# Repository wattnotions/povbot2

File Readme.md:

# POVbot - A Small Pi Zero FPV Robot

## 3d Print Files

Look in 3d_print folder to find a 3mf file with the chassis , camera holder and wheels ready to print.

## Software

Setting up video streaming and remote control is very easy.

Clone this repo to a raspberry pi, navigate to web_server/keyandvid/

From there run "python app.py" and the web server will start

Then you can navigate to your pis ip address using a computer on the same wifi. Use port 8000.

For example : 192.168.0.186:8000 and you should see your video stream. The robot can be steered using the WASD keys on your keyboard

## PCB Files

The hat was designed in Kicad 7. All project files are in kicad_files.

The board was made and assembled by PCBway. If you wish to get your own board assembled using PCBway look in kicad_files/pcbway_production for all of the required PCB manufacture and assembly files, ready for upload to JLCPCB.

## Youtube video

I made a short video explaining the project. It is available here:

[Watch the video](https://www.youtube.com/watch?v=tIp2PrZHXOc)

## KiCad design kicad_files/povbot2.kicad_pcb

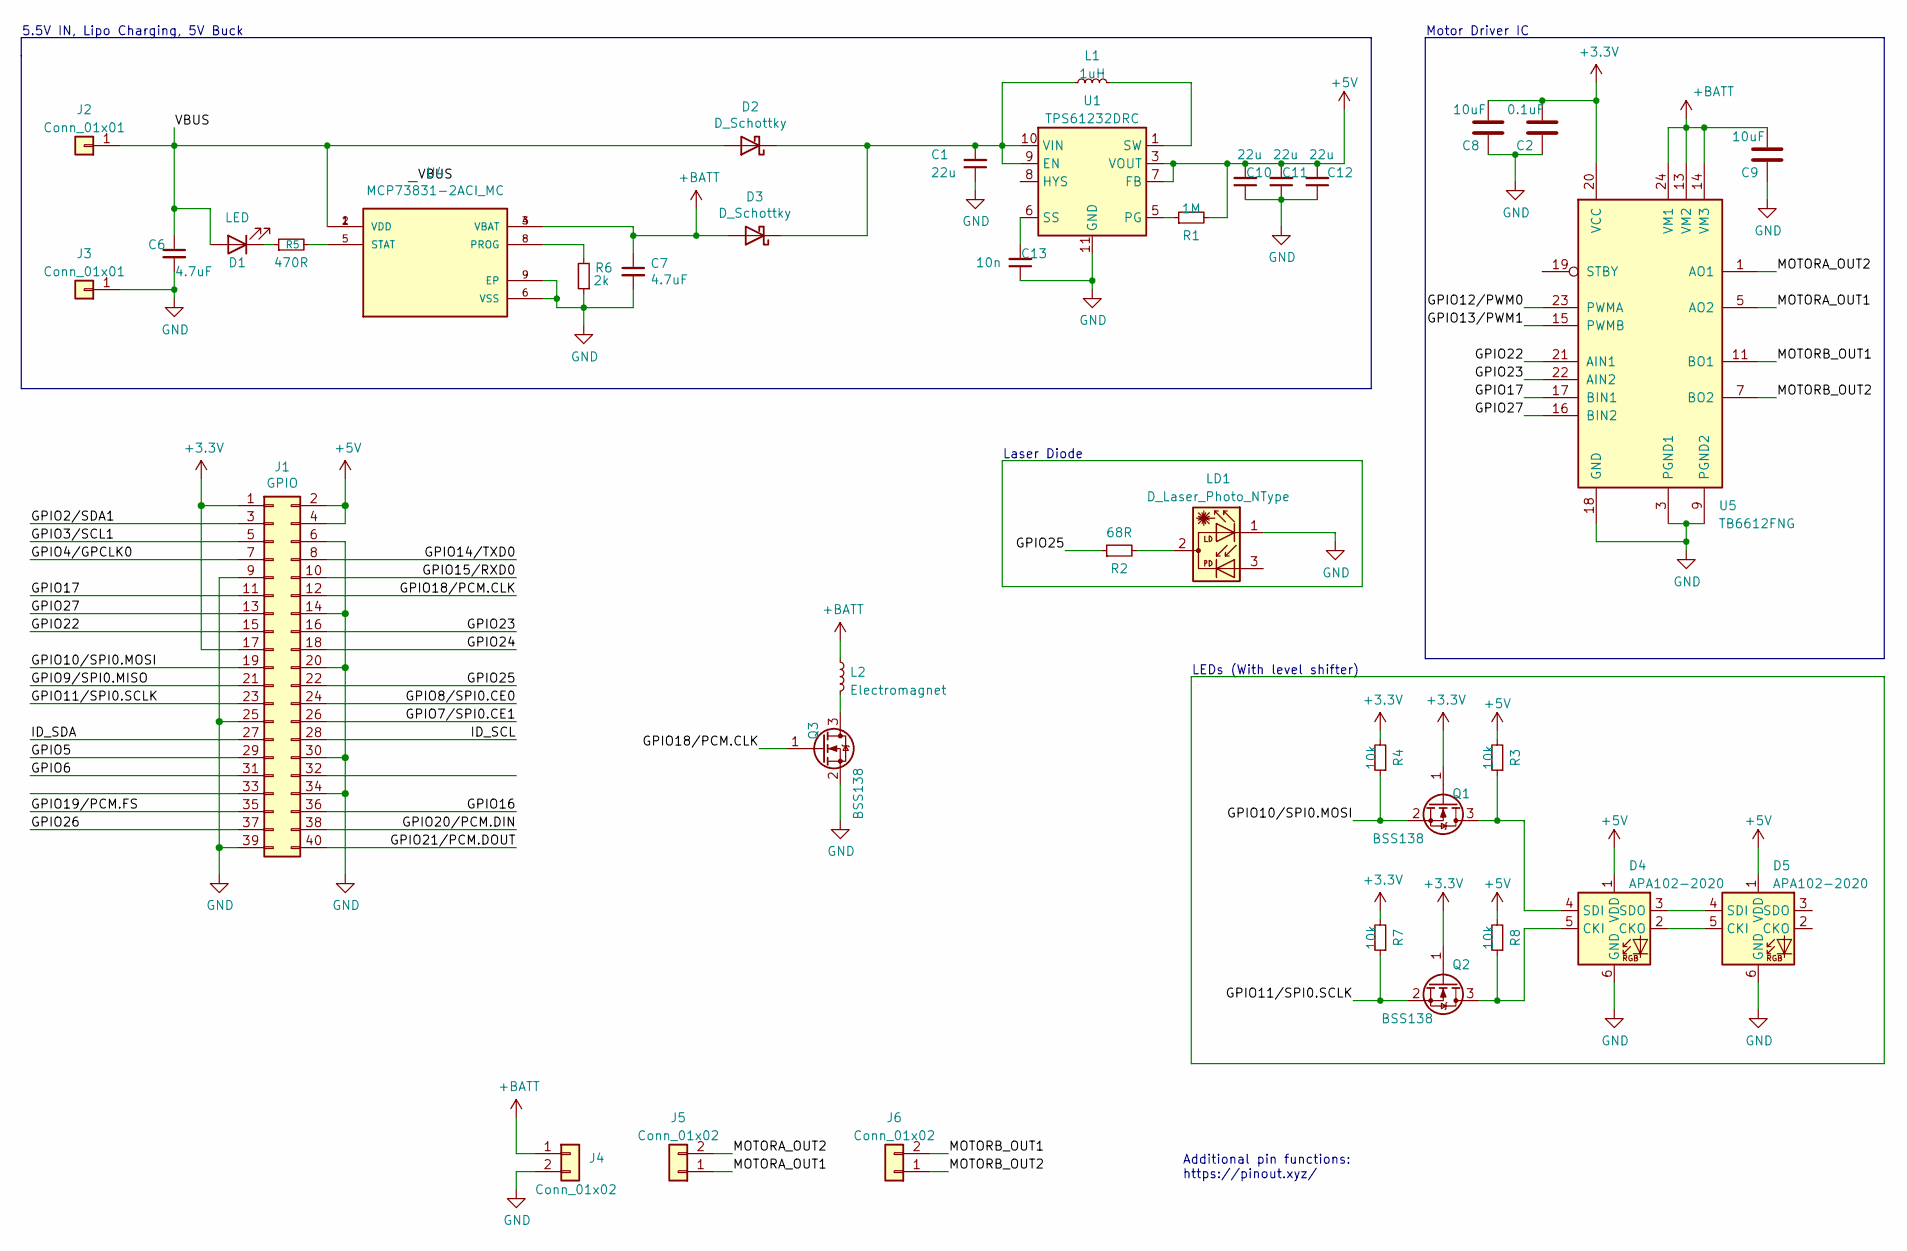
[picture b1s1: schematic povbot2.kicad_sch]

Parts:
C1: 22u
C2: 0.1uF; C_0603_1608Metric
C6, C7: 4.7uF; C_0603_1608Metric
C8, C9: 10uF; C_0603_1608Metric
C10, C11, C12: 22u; C_0805_2012Metric
C13: 10n; C_0402_1005Metric
D1: LED; LED_0402_1005Metric
D2, D3: D_Schottky; D_SOD-323; LCSC C146335
D4, D5: APA102-2020; LED-APA102-2020
J1: GPIO; PinSocket_2x20_P2.54mm_Vertical
J2, J3: Conn_01x01; PinHeader_1x01_P2.54mm_Vertical
J4: Conn_01x02; Molex_PicoBlade_53398-0271_1x02-1MP_P1.25mm_Vertical
J5, J6: Conn_01x02; Molex_PicoBlade_53261-0271_1x02-1MP_P1.25mm_Horizontal
L1: 1uH; L_0402_1005Metric
L2: Electromagnet; PinHeader_1x02_P2.54mm_Vertical
LD1: D_Laser_Photo_NType; LaserDiode_TO18-D5.6-3
Q1, Q2, Q3: BSS138; SOT-23
R1: 1M; R_0603_1608Metric
R2: 68R; R_0603_1608Metric
R3, R4, R7, R8: 10k; R_0603_1608Metric
R5: 470R; R_0603_1608Metric
R6: 2k; R_0603_1608Metric
U1: TPS61232DRC; Texas_S-PVSON-N10_ThermalVias
U4: MCP73831-2ACI_MC; SON50P200X300X100-9N; PARTREV G; LCSC C150772
U5: TB6612FNG; SSOP-24_5.3x8.2mm_P0.65mm

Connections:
+3V3: C2.1, C8.1, J1.1, J1.17, Q1.1 (G), Q2.1 (G), R4.2, R7.2, U5.20 (VCC)
+5V: C10.2, C11.2, C12.2, D4.1 (VDD), D5.1 (VDD), J1.2, J1.4, R1.2, R3.2, R8.2, U1.3 (VOUT), U1.4 (VOUT), U1.7 (FB)
+BATT: C7.1, C9.1, D3.2 (A), J4.1, L2.1, U4.3 (VBAT), U4.4 (VBAT), U5.13 (VM2), U5.14 (VM3), U5.24 (VM1)
/GPIO2/SDA1: J1.3
/GPIO3/SCL1: J1.5
/GPIO4/GPCLK0: J1.7
/GPIO5: J1.29
/GPIO6: J1.31
/GPIO7/SPI0.CE1: J1.26
/GPIO8/SPI0.CE0: J1.24
/GPIO9/SPI0.MISO: J1.21
/GPIO10/SPI0.MOSI: J1.19, Q1.2 (S), R4.1
/GPIO11/SPI0.SCLK: J1.23, Q2.2 (S), R7.1
/GPIO12/PWM0: U5.23 (PWMA)
/GPIO13/PWM1: U5.15 (PWMB)
/GPIO14/TXD0: J1.8
/GPIO15/RXD0: J1.10
/GPIO16: J1.36
/GPIO17: J1.11, U5.17 (BIN1)
/GPIO18/PCM.CLK: J1.12, Q3.1 (G)
/GPIO19/PCM.FS: J1.35
/GPIO20/PCM.DIN: J1.38
/GPIO21/PCM.DOUT: J1.40
/GPIO22: J1.15, U5.21 (AIN1)
/GPIO23: J1.16, U5.22 (AIN2)
/GPIO24: J1.18
/GPIO25: J1.22, R2.1
/GPIO26: J1.37
/GPIO27: J1.13, U5.16 (BIN2)
/ID_SCL: J1.28
/ID_SDA: J1.27
/MOTORA_OUT1: J5.1, U5.5 (AO2), U5.6 (AO2)
/MOTORA_OUT2: J5.2, U5.1 (AO1), U5.2 (AO1)
/MOTORB_OUT1: J6.2, U5.11 (BO1), U5.12 (BO1)
/MOTORB_OUT2: J6.1, U5.7 (BO2), U5.8 (BO2)
/VBUS: C6.1, D1.2 (A), D2.2 (A), J2.1, U4.1 (VDD), U4.2 (VDD)
GND: C1.1, C2.2, C6.2, C7.2, C8.2, C9.2, C10.1, C11.1, C12.1, C13.1, D4.6 (GND), D5.6 (GND), J1.6, J1.9, J1.14, J1.20, J1.25, J1.30, J1.34, J1.39, J3.1, J4.2, LD1.1, Q3.2 (S), R6.1, U1.11 (GND), U4.6 (VSS), U4.9 (EP), U5.3 (PGND1), U5.4 (PGND1), U5.9 (PGND2), U5.10 (PGND2), U5.18 (GND)
unnamed: D1.1 (K), R5.1
unnamed: C1.2, D2.1 (K), D3.1 (K), L1.1, U1.9 (EN), U1.10 (VIN)
unnamed: D4.5 (CKI), Q2.3 (D), R8.1
unnamed: D4.2 (CKO), D5.5 (CKI)
unnamed: D4.4 (SDI), Q1.3 (D), R3.1
unnamed: D4.3 (SDO), D5.4 (SDI)
unnamed: L1.2, U1.1 (SW), U1.2 (SW)
unnamed: LD1.2, R2.2
unnamed: L2.2, Q3.3 (D)
unnamed: R1.1, U1.5 (PG)
unnamed: C13.2, U1.6 (SS)
unnamed: R6.2, U4.8 (PROG)
unnamed: R5.2, U4.5 (STAT)

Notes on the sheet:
Motor Driver IC
Laser Diode
5.5V IN, Lipo Charging, 5V Buck
LEDs (With level shifter)
Additional pin functions: https://pinout.xyz/

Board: 2 copper layers, 40 parts (1 on the bottom side), 28 nets, no tracks yet.

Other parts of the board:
MH1, MH2, MH3, MH4: MountingHole_2.7mm_M2.5

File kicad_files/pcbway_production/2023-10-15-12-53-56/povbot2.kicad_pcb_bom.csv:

designator,quantity,value,pack,mpn,mount_type
C1,1,22u,C_0603_1608Metric,,smt
"C10, C11, C12",3,22u,C_0805_2012Metric,,smt
C13,1,10n,C_0603_1608Metric,,smt
C2,1,0.1uF,C_0603_1608Metric,,smt
"C6, C7",2,4.7uF,C_0603_1608Metric,,smt
"C8, C9",2,10uF,C_0603_1608Metric,,smt
D1,1,LED,LED_0603_1608Metric,,smt
"D2, D3",2,D_Schottky,D_SOD-323,SBA120CS_R1_00001,smt
J1,1,GPIO,PinSocket_2x20_P2.54mm_Vertical,61304021121,tht
"J4, J5, J6",3,Conn_01x02,JST_PH_B2B-PH-K_1x02_P2.00mm_Vertical,B2B-PH-K-S,tht
J7,1,USB_B_Micro,USB_Micro-B_Molex_47346-0001,0473460001,smt
L1,1,1uH,IND_SRP4020TA-1R0M,SRP4020TA-1R0M,smt
"MH1, MH2, MH3, MH4",4,MountingHole_2.7mm_M2.5,MountingHole_2.7mm_M2.5,,tht
R1,1,1M,R_0603_1608Metric,,smt
R5,1,470R,R_0603_1608Metric,,smt
R6,1,2k,R_0603_1608Metric,,smt
U1,1,TPS61232DRC,Texas_S-PVSON-N10_ThermalVias,TPS61232DRCR,smt
U4,1,MCP73831-2ACI_MC,SON50P200X300X100-9N,MCP73831-2ACI/MC,tht
U5,1,TB6612FNG,SSOP-24_5.3x8.2mm_P0.65mm,"TB6612FNG,C,8,EL",smt

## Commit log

2023-06-26 initial
2023-07-03 added motor driver IC, BOM, laser diode, LEDs, and electomagnet
2023-07-31 started pcb, added foorprints etc
2023-08-02 floorplanning done
2023-10-15 changed inductor larger package 5A current version, made pcbway fab files
2023-11-04 test commit
2023-11-04 added working video stream example
2023-11-04 got basic keypress detection example working
2023-11-04 working keypress with python output
2023-11-04 added test script dir
2023-11-04 got vid stream + keypress in one webpage working
2023-11-04 working vid with remote control buttons
2023-11-04 rotated cam by 90 degrees ccw
2023-11-06 rotated cam 90 degrees ccw
2023-11-06 removed js keypress text but kepy detection
2023-11-06 got basic 3 column html template going
2023-11-09 added 3mf preview
2023-11-09 added 3mf print file
2023-11-09 cleaned up dir structure
2023-11-09 renamed website folder to web server for clarity
2023-11-10 updated folder name
2023-11-10 moved old stuff to test scripts folder
